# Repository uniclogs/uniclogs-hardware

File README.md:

# University Class Open Ground Station
UniClOGS ground station hardware for both RF and antenna positioning

## OreSat Ground Station Infrastructure

OreSat will utilize two ground stations for this project, a primary station, and a fully-capable secondary station. The primary station is being constructed by the students involved in the project and will be located on the Portland State University Engineering Building. The secondary station is an existing amateur satellite ground station located at a different location for spatial diversity. It can be used to help verify and check out the primary station as construction progresses, and serve as a backup to the primary station. The two stations are identical.

## RF Links

The ground station infrastructure provides two communications functions between the ground and the spacecraft, (1) downlink communications on UHF for the Telemetry Beacons and Command Responses from the spacecraft, (2) uplink communications on L-Band for the Commands to the spacecraft, and (3) downlink communications on S-band for mission payload and camera data.

The UHF component is centered in the 435 to 438 MHz amateur spacecraft service band and utilizes a circular polarized directional Yagi antenna with a RHCP/LHCP polarization sense switch. The L-Band component is centered in the 1260 to 1270 MHz amateur spacecraft service band designated for uplink only, and utilizes a RHCP circular polarized 2x2 helix array. All of this is mounted on an azimuth/elevation antenna positioner. A coax switch connects the UHF antenna to either a Low Noise Amplifier (LNA) for receiving, or a Power Amplifier (PA) for transmitting. The LNA and PA is then connected to a Software Defined Radio (SDR) that provides both UHF RF input and output signals. The L-Band antenna is directly connected to a PA for transmitting only, and then to the same SDR to provide the L Band RF signal.

The S-Band component is centered on 2.4 to 2.43 GHz amateur spacecraft service spectrum. A 0.5 meter parabolic reflector with a RHCP/LHCP feed is mounted on the same antenna positioner as the UHF and L-Band antenna. A coax switch is used to select RHCP or LHCP signal from the feed, is then fed to a bidirectional PA/LNA. The PA/LNA is connected to a ATH9K IEEE 802.11b adapter that provides both the S-Band RF downlink receiver and uplink transmitter signals.

The SDR used for UHF and L-Band is the LimeSDR from LimeMicro, which utilizes GnuRadio for modulation and demodulation. The emission type is GFSK at 50 kb/s, and was chosen for the capability of the Engineering transceiver radio on the spacecraft, an acceptable performance indicated by the link budget, and is somewhat common in the amateur satellite community.

## Antenna positioner

An antenna positioner controller is used to aim the antenna array and is interfaced serially using the EasyComm control protocol accessible through the HamLib control library. The positioner controller is based on the Open Source hardware/software project by K3NG, and provides the ability for tracking control through HamLib _rotctld_ both locally using GPredict, or by the SatNOGS Client software which provides interconnectivity to the SatNOGS system over the Internet.

## GnuRadio 

Data is passed into/out of the ground station radio through GnuRadio ModCod blocks and can provide raw IQ sample files from the payload data. Doppler shift can be compensated for in real time using the tracking software and an XML/RPC server in GnuRadio.

## Data

The Engineering Control/Telemetry subsystem provides telemetry data to the ground in two forms, a GFSK modulated data frame in response to a command request, and a very short Morse code (CW) modulated telemetry sequence and satellite ID if no activity is present for a given period of time. This Morse code ID allows the satellite to be heard by the general amateur radio community and will help with identifying the satellite once on orbit. There are several satellite housekeeping commands that can be sent up from the ground to control power, attitude and payload functions, and most importantly a command to reliably shut off all RF transmissions if required. All commands up to the satellite are authenticated for security.

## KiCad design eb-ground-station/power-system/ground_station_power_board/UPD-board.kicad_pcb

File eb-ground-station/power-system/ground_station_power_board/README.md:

# Station Power Board

This board controls all of the switching of power to components in the ground station.
It accepts it's commands through an I2C interface on the Stationd computer.

The switching is acomplished through 3 I2C GPIO device setup as 24 output bits. The
bits control mosfet switches provideing both 5VDC and 12VDC circuits.

The board also has an A/D to monitor the RF Power Amplifiers output power detectors. The
characteristics of this power measurement is detailed in the power amplifier testing
spreadsheet unfer RF-systems.

Finally this board provides a temperature measurement of the system enclosures environment.

See further documentation in the docs folder

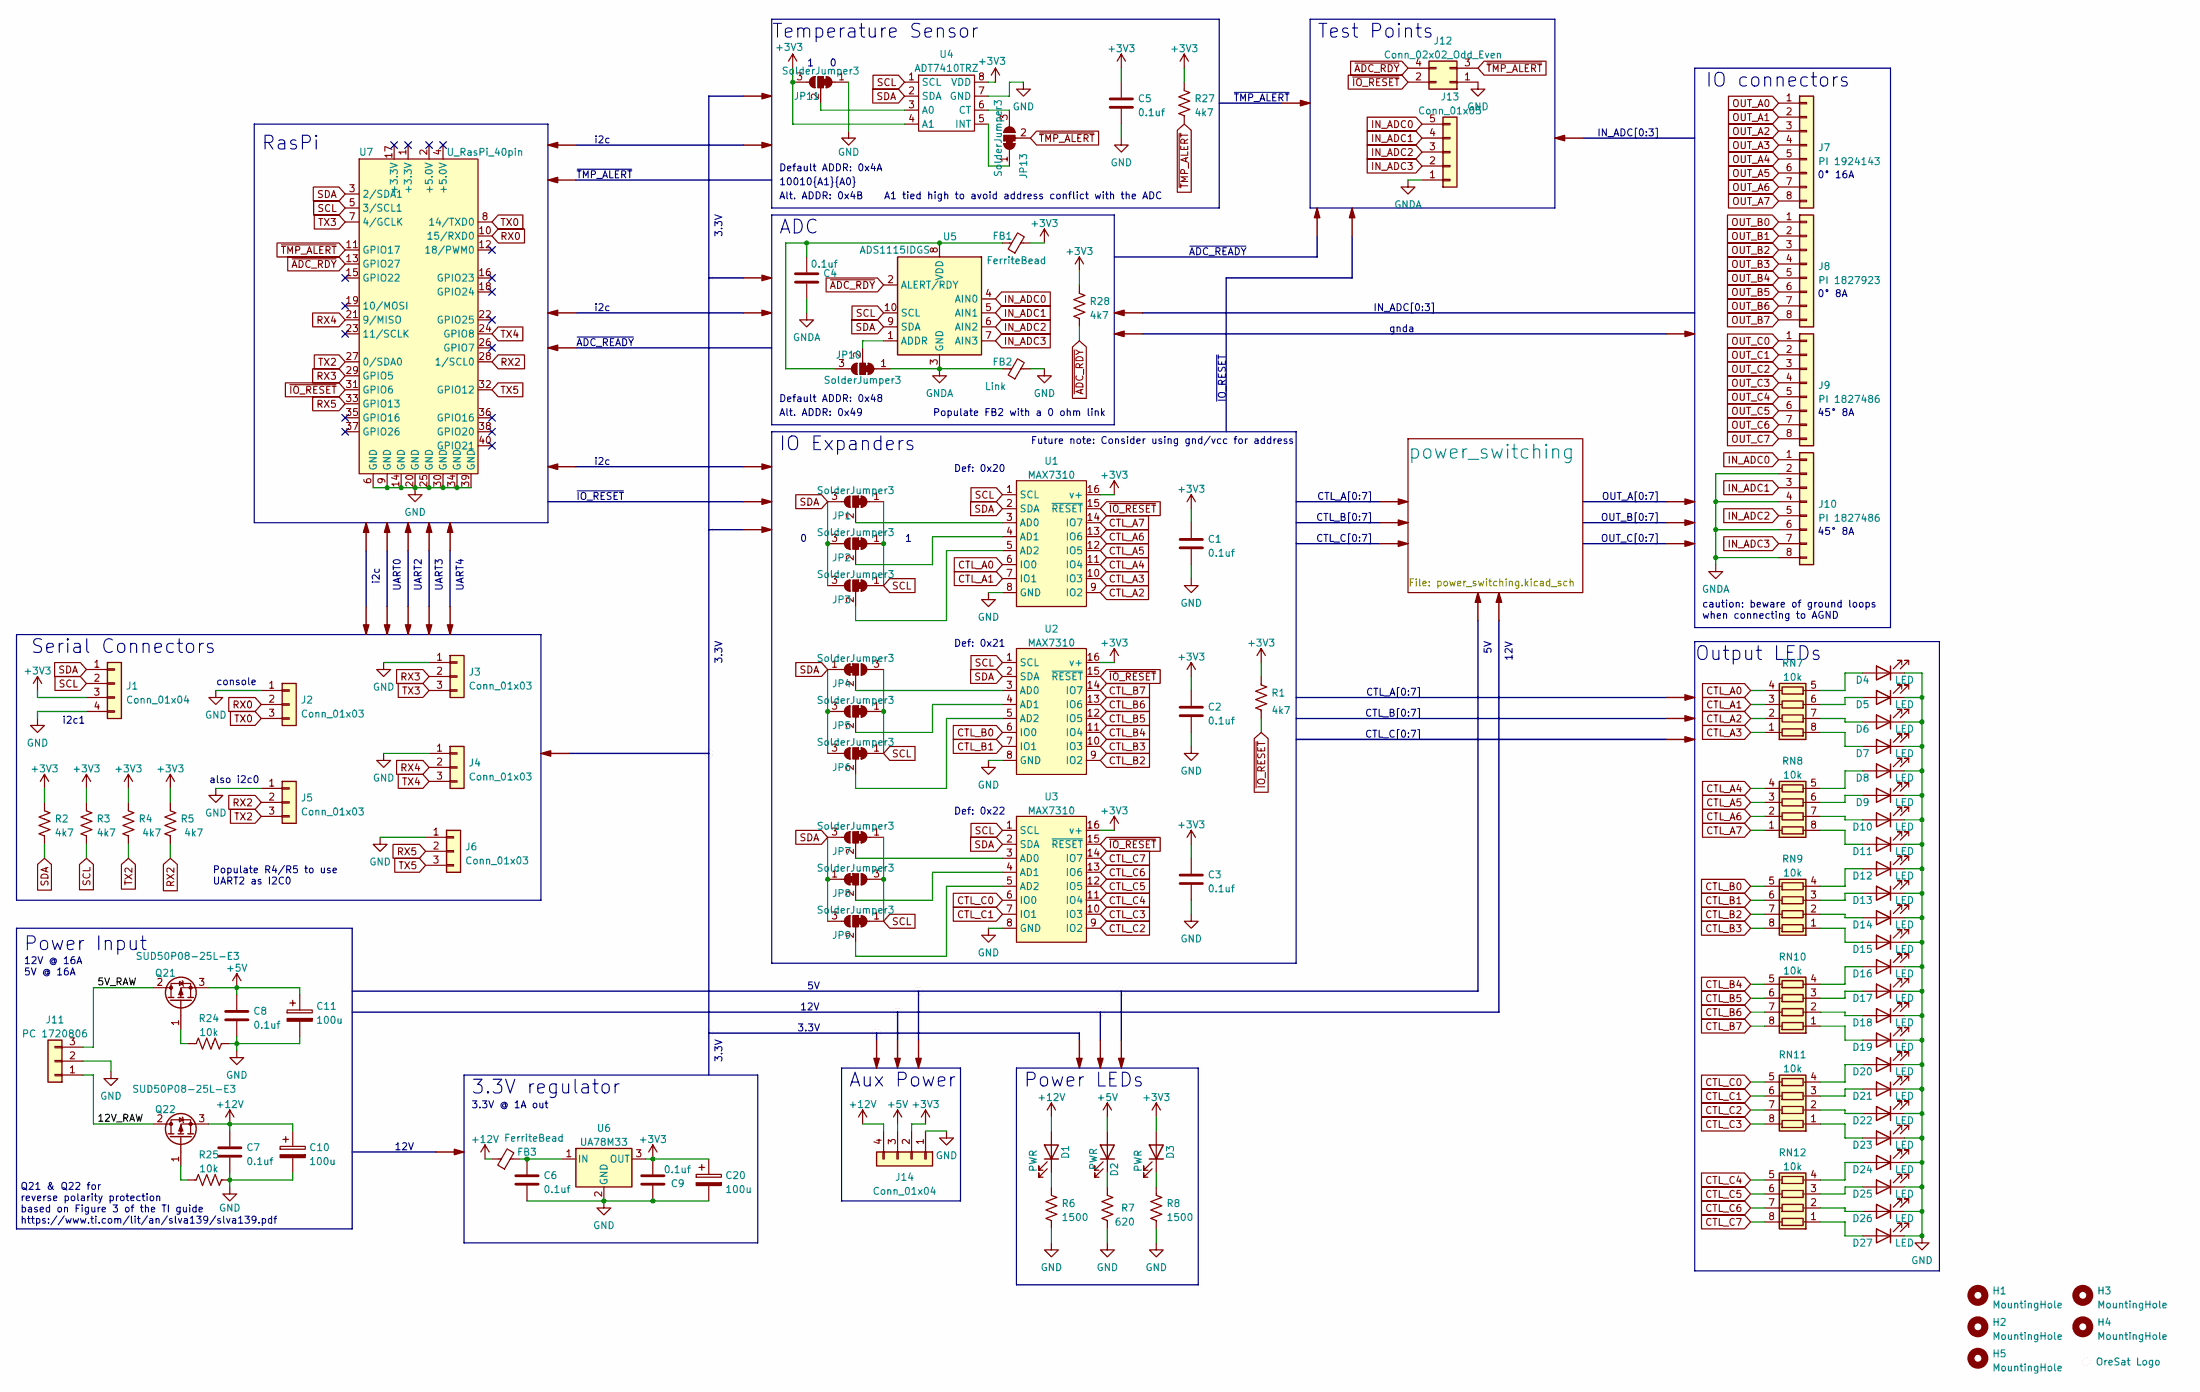
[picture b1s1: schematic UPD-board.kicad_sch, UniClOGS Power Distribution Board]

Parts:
C1, C2, C3, C4, C5, C6, C7, C8, C9: 0.1uf; C_0603_1608Metric; MPN CL10B104KB8NNWC
C10, C11, C20: 100u; CP_Elec_6.3x5.9; MPN 865080445010
D1, D2, D3: PWR; LED_0603_1608Metric
D4, D5, D6, D7, D8, D9, D10, D11, D12, D13, D14, D15, D16, D17, D18, D19, D20, D21, D22, D23, D24, D25, D26, D27: LED; LED_0603_1608Metric
FB1, FB3: FerriteBead; C_0805_2012Metric; MPN WLBD2012HCU310TH
FB2: Link; R_0805_2012Metric
H1, H2, H3, H4, H5: MountingHole; H-MCMASTER-94100A150
J1, J14: Conn_01x04; PinHeader_1x04_P2.54mm_Vertical
J2, J3, J4, J5, J6: Conn_01x03; PinHeader_1x03_P2.54mm_Vertical
J7: PI 1924143; J_PhoenixContact_MC_1,5_8-GF-5.08_1x08_P5.08mm_Horizontal_T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
J8: PI 1827923; PhoenixContact_MC_1,5_8-GF-3.81_1x08_P3.81mm_Horizontal_Thr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
J9, J10: PI 1827486; J_PhoenixContact_MC_1,5_8-GF-3.81_1x08_P3.81mm_45degree_Thr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
J11: PC 1720806; PhoenixContact_GMSTBA_2,5_3-G-7,62_1x03_P7.62mm_Horizontal
J12: Conn_02x02_Odd_Even; PinHeader_2x02_P2.54mm_Vertical
J13: Conn_01x05; PinHeader_1x05_P2.54mm_Vertical
JP1, JP2, JP3, JP4, JP5, JP6, JP7, JP8, JP9, JP10, JP11, JP13: SolderJumper3; SolderJumper-3_P1.3mm_Bridged12_Pad1.0x1.5mm
LOGO1: OreSat Logo; logo-small
Q21, Q22: SUD50P08-25L-E3; TO-252-3_TabIsPin2
R1, R2, R3, R4, R5, R27, R28: 4k7; R_0603_1608Metric
R6, R8: 1500; R_0603_1608Metric
R7: 620; R_0603_1608Metric
R24, R25: 10k; R_0603_1608Metric
RN7, RN8, RN9, RN10, RN11, RN12: 10k; R_Array_Convex_4x0603; MPN RAVF164DJT10K0
U1, U2, U3: MAX7310; TSSOP-16_4.4x5mm_P0.65mm; MPN MAX7310ATE+T
U4: ADT7410TRZ; SOIC-8_3.9x4.9mm_P1.27mm
U5: ADS1115IDGS; TSSOP-10_3x3mm_P0.5mm
U6: UA78M33; SOT-223-3_TabPin2
U7: U_RasPi_40pin; IDC-Header_2x20_P2.54mm_Vertical

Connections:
+3V3: C1.1, C2.1, C3.1, C5.1, C9.1, C20.1, D3.2 (A), FB1.2, J1.3, J14.2, JP11.3 (B), R1.1, R2.1, R3.1, R4.1, R5.1, R27.1, R28.1, U1.16 (v+), U2.16 (v+), U3.16 (v+), U4.4 (A1), U4.8 (VDD), U6.3 (OUT); also elsewhere on the board
+5V: C8.2, C11.1, D2.2 (A), J14.3, Q21.3 (S); also elsewhere on the board
+12V: C7.1, C10.1, D1.2 (A), FB3.1, J14.4, Q22.3 (S); also elsewhere on the board
/5V_RAW: J11.3, Q21.2 (D)
/12V_RAW: J11.1, Q22.2 (D)
CTL_A0: RN7.4 (R4.1), U1.6 (IO0); also elsewhere on the board
CTL_A1: RN7.3 (R3.1), U1.7 (IO1); also elsewhere on the board
CTL_A2: RN7.2 (R2.1), U1.9 (IO2); also elsewhere on the board
CTL_A3: RN7.1 (R1.1), U1.10 (IO3); also elsewhere on the board
CTL_A4: RN8.4 (R4.1), U1.11 (IO4); also elsewhere on the board
CTL_A5: RN8.3 (R3.1), U1.12 (IO5); also elsewhere on the board
CTL_A6: RN8.2 (R2.1), U1.13 (IO6); also elsewhere on the board
CTL_A7: RN8.1 (R1.1), U1.14 (IO7); also elsewhere on the board
CTL_B0: RN9.5 (R4.2), U2.6 (IO0); also elsewhere on the board
CTL_B1: RN9.6 (R3.2), U2.7 (IO1); also elsewhere on the board
CTL_B2: RN9.7 (R2.2), U2.9 (IO2); also elsewhere on the board
CTL_B3: RN9.8 (R1.2), U2.10 (IO3); also elsewhere on the board
CTL_B4: RN10.5 (R4.2), U2.11 (IO4); also elsewhere on the board
CTL_B5: RN10.6 (R3.2), U2.12 (IO5); also elsewhere on the board
CTL_B6: RN10.7 (R2.2), U2.13 (IO6); also elsewhere on the board
CTL_B7: RN10.8 (R1.2), U2.14 (IO7); also elsewhere on the board
CTL_C0: RN11.5 (R4.2), U3.6 (IO0); also elsewhere on the board
CTL_C1: RN11.6 (R3.2), U3.7 (IO1); also elsewhere on the board
CTL_C2: RN11.7 (R2.2), U3.9 (IO2); also elsewhere on the board
CTL_C3: RN11.8 (R1.2), U3.10 (IO3); also elsewhere on the board
CTL_C4: RN12.5 (R4.2), U3.11 (IO4); also elsewhere on the board
CTL_C5: RN12.6 (R3.2), U3.12 (IO5); also elsewhere on the board
CTL_C6: RN12.7 (R2.2), U3.13 (IO6); also elsewhere on the board
CTL_C7: RN12.8 (R1.2), U3.14 (IO7); also elsewhere on the board
GND: C1.2, C2.2, C3.2, C5.2, C6.2, C7.2, C8.1, C9.2, C10.2, C11.2, C20.2, D4.1 (K), D5.1 (K), D6.1 (K), D7.1 (K), D8.1 (K), D9.1 (K), D10.1 (K), D11.1 (K), D12.1 (K), D13.1 (K), D14.1 (K), D15.1 (K), D16.1 (K), D17.1 (K), D18.1 (K), D19.1 (K), D20.1 (K), D21.1 (K), D22.1 (K), D23.1 (K), D24.1 (K), D25.1 (K), D26.1 (K), D27.1 (K), FB2.2, J1.4, J2.1, J3.1, J4.1, J5.1, J6.1, J11.2, J12.1, J14.1, JP11.1 (A), R6.1, R7.2, R8.1, R24.1, R25.1, U1.8 (GND), U2.8 (GND), U3.8 (GND), U4.7 (GND), U6.2 (GND), U7.6 (GND), U7.9 (GND), U7.14 (GND), U7.20 (GND), U7.25 (GND), U7.30 (GND), U7.34 (GND), U7.39 (GND); also elsewhere on the board
GNDA: C4.2, FB2.1, J10.2, J10.4, J10.6, J10.8, J13.1, JP10.1 (A), U5.3 (GND)
IN_ADC0: J10.1, J13.5, U5.4 (AIN0)
IN_ADC1: J10.3, J13.4, U5.5 (AIN1)
IN_ADC2: J10.5, J13.3, U5.6 (AIN2)
IN_ADC3: J10.7, J13.2, U5.7 (AIN3)
unnamed: C4.1, FB1.1, JP10.3 (B), U5.8 (VDD)
unnamed: C6.1, FB3.2, U6.1 (IN)
unnamed: D1.1 (K), R6.2
unnamed: D2.1 (K), R7.1
unnamed: D3.1 (K), R8.2
unnamed: D4.2 (A), RN7.5 (R4.2)
unnamed: D5.2 (A), RN7.6 (R3.2)
unnamed: D6.2 (A), RN7.7 (R2.2)
unnamed: D7.2 (A), RN7.8 (R1.2)
unnamed: D8.2 (A), RN8.5 (R4.2)
unnamed: D9.2 (A), RN8.6 (R3.2)
unnamed: D10.2 (A), RN8.7 (R2.2)
unnamed: D11.2 (A), RN8.8 (R1.2)
unnamed: D12.2 (A), RN9.4 (R4.1)
unnamed: D13.2 (A), RN9.3 (R3.1)
unnamed: D14.2 (A), RN9.2 (R2.1)
unnamed: D15.2 (A), RN9.1 (R1.1)
unnamed: D16.2 (A), RN10.4 (R4.1)
unnamed: D17.2 (A), RN10.3 (R3.1)
unnamed: D18.2 (A), RN10.2 (R2.1)
unnamed: D19.2 (A), RN10.1 (R1.1)
unnamed: D20.2 (A), RN11.4 (R4.1)
unnamed: D21.2 (A), RN11.3 (R3.1)
unnamed: D22.2 (A), RN11.2 (R2.1)
unnamed: D23.2 (A), RN11.1 (R1.1)
unnamed: D24.2 (A), RN12.4 (R4.1)
unnamed: D25.2 (A), RN12.3 (R3.1)
unnamed: D26.2 (A), RN12.2 (R2.1)
unnamed: D27.2 (A), RN12.1 (R1.1)
unnamed: JP1.2 (C), U1.3 (AD0)
unnamed: JP2.2 (C), U1.4 (AD1)
unnamed: JP3.2 (C), U1.5 (AD2)
unnamed: JP4.2 (C), U2.3 (AD0)
unnamed: JP5.2 (C), U2.4 (AD1)
unnamed: JP6.2 (C), U2.5 (AD2)
unnamed: JP7.2 (C), U3.3 (AD0)
unnamed: JP8.2 (C), U3.4 (AD1)
unnamed: JP9.2 (C), U3.5 (AD2)
unnamed: JP10.2 (C), U5.1 (ADDR)
unnamed: JP11.2 (C), U4.3 (A0)
unnamed: JP13.1 (A), U4.5 (INT)
unnamed: JP13.3 (B), U4.6 (CT)
unnamed: Q21.1 (G), R24.2
unnamed: Q22.1 (G), R25.2
OUT_A0: J7.1; also elsewhere on the board
OUT_A1: J7.2; also elsewhere on the board
OUT_A2: J7.3; also elsewhere on the board
OUT_A3: J7.4; also elsewhere on the board
OUT_A4: J7.5; also elsewhere on the board
OUT_A5: J7.6; also elsewhere on the board
OUT_A6: J7.7; also elsewhere on the board
OUT_A7: J7.8; also elsewhere on the board
OUT_B0: J8.1; also elsewhere on the board
OUT_B1: J8.2; also elsewhere on the board
OUT_B2: J8.3; also elsewhere on the board
OUT_B3: J8.4; also elsewhere on the board
OUT_B4: J8.5; also elsewhere on the board
OUT_B5: J8.6; also elsewhere on the board
OUT_B6: J8.7; also elsewhere on the board
OUT_B7: J8.8; also elsewhere on the board
OUT_C0: J9.1; also elsewhere on the board
OUT_C1: J9.2; also elsewhere on the board
OUT_C2: J9.3; also elsewhere on the board
OUT_C3: J9.4; also elsewhere on the board
OUT_C4: J9.5; also elsewhere on the board
OUT_C5: J9.6; also elsewhere on the board
OUT_C6: J9.7; also elsewhere on the board
OUT_C7: J9.8; also elsewhere on the board
RX0: J2.2, U7.10 (15/RXD0)
RX2: J5.2, R5.2, U7.28 (1/SCL0)
RX3: J3.2, U7.29 (GPIO5)
RX4: J4.2, U7.21 (9/MISO)
RX5: J6.2, U7.33 (GPIO13)
SCL: J1.2, JP1.1 (A), JP2.1 (A), JP3.1 (A), JP4.3 (B), JP5.1 (A), JP6.1 (A), JP7.1 (A), JP8.3 (B), JP9.1 (A), R3.2, U1.1 (SCL), U2.1 (SCL), U3.1 (SCL), U4.1 (SCL), U5.10 (SCL), U7.5 (3/SCL1)
SDA: J1.1, JP1.3 (B), JP2.3 (B), JP3.3 (B), JP4.1 (A), JP5.3 (B), JP6.3 (B), JP7.3 (B), JP8.1 (A), JP9.3 (B), R2.2, U1.2 (SDA), U2.2 (SDA), U3.2 (SDA), U4.2 (SDA), U5.9 (SDA), U7.3 (2/SDA1)
TX0: J2.3, U7.8 (14/TXD0)
TX2: J5.3, R4.2, U7.27 (0/SDA0)
TX3: J3.3, U7.7 (4/GCLK)
TX4: J4.3, U7.24 (GPIO8)
TX5: J6.3, U7.32 (GPIO12)
~ADC_RDY: J12.4, R28.2, U5.2 (ALERT/RDY), U7.13 (GPIO27)
~IO_RESET: J12.2, R1.2, U1.15 (~RESET), U2.15 (~RESET), U3.15 (~RESET), U7.31 (GPIO6)
~TMP_ALERT: J12.3, JP13.2 (C), R27.2, U7.11 (GPIO17)

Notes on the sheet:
12V
UART4
OUT_A[0:7]
~{ADC_READY}
3.3V
Power Input
UART2
45° 8A
Test Points
Alt. ADDR: 0x4B
Def: 0x20
3.3V @ 1A out
OUT_C[0:7]
Serial Connectors
OUT_B[0:7]
Def: 0x21
0° 16A
also i2c0
CTL_A[0:7]
Def: 0x22
CTL_C[0:7]
Temperature Sensor
CTL_B[0:7]
UART0
12V @ 16A 5V @ 16A
caution: beware of ground loops when connecting to AGND
IN_ADC[0:3]
0° 8A
A1 tied high to avoid address conflict with the ADC
Alt. ADDR: 0x49
Output LEDs
~{TMP_ALERT}
RasPi
i2c
Aux Power
Populate R4/R5 to use UART2 as I2C0
Default ADDR: 0x48
IO connectors
Power LEDs
~{IO_RESET}

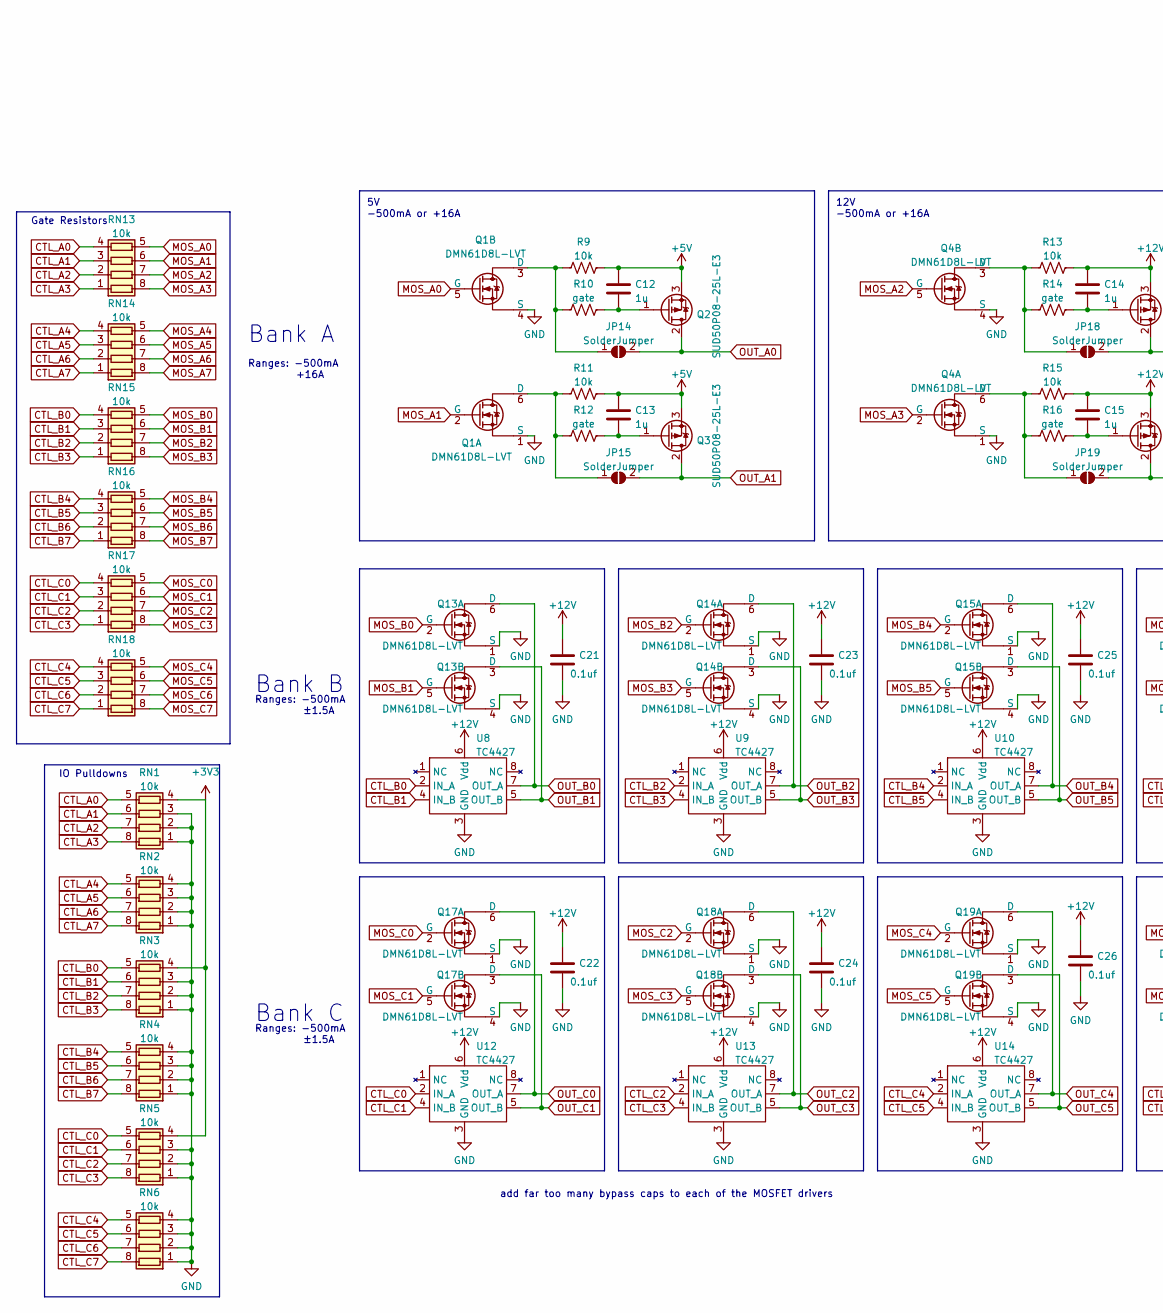
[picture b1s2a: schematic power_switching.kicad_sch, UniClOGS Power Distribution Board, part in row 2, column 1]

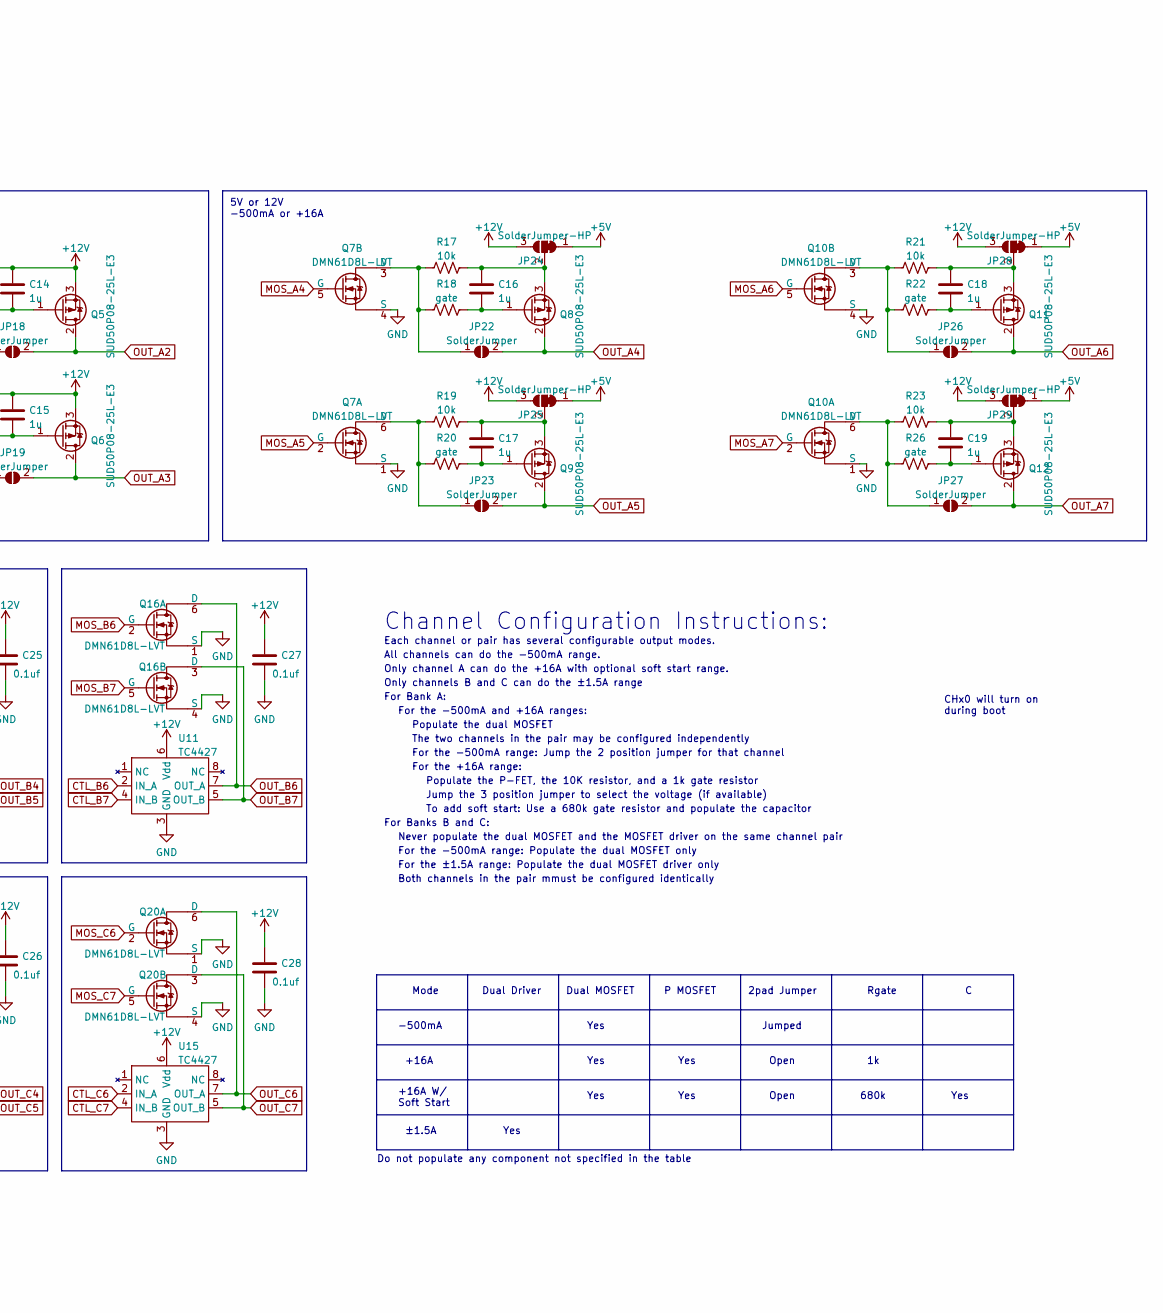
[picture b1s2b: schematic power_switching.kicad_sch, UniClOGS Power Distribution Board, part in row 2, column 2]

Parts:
C12, C13, C14, C15, C16, C17, C18, C19: 1u; C_0603_1608Metric; MPN CL10B105KA8NNNC
C21, C22, C23, C24, C25, C26, C27, C28: 0.1uf; C_0603_1608Metric; MPN CL10B104KB8NNWC
JP14, JP15, JP18, JP19, JP22, JP23, JP26, JP27: SolderJumper; SolderJumper-2_P1.3mm_Open_RoundedPad1.0x1.5mm
JP24, JP25, JP28, JP29: SolderJumper-HP; JP-SOLDER-2way-HP
Q1, Q4, Q7, Q10, Q13, Q14, Q15, Q16, Q17, Q18, Q19, Q20: DMN61D8L-LVT; TSOT26-6
Q2, Q3, Q5, Q6, Q8, Q9, Q11, Q12: SUD50P08-25L-E3; TO-252-3_TabIsPin2
R9, R11, R13, R15, R17, R19, R21, R23: 10k; R_0603_1608Metric
R10, R12, R14, R16, R18, R20, R22, R26: gate; R_0603_1608Metric
RN1, RN2, RN3, RN4, RN5, RN6, RN13, RN14, RN15, RN16, RN17, RN18: 10k; R_Array_Convex_4x0603; MPN RAVF164DJT10K0
U8, U9, U10, U11, U12, U13, U14, U15: TC4427; MSOP-8_3x3mm_P0.65mm

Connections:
+3V3: RN1.4 (R4.1), RN3.4 (R4.1), RN5.4 (R4.1); also elsewhere on the board
+5V: C12.1, C13.1, JP24.1 (A), JP25.1 (A), JP28.1 (A), JP29.1 (A), Q2.3 (S), Q3.3 (S), R9.2, R11.2; also elsewhere on the board
+12V: C14.1, C15.1, C21.1, C22.1, C23.1, C24.1, C25.1, C26.1, C27.1, C28.1, JP24.3 (B), JP25.3 (B), JP28.3 (B), JP29.3 (B), Q5.3 (S), Q6.3 (S), R13.2, R15.2, U8.6 (Vdd), U9.6 (Vdd), U10.6 (Vdd), U11.6 (Vdd), U12.6 (Vdd), U13.6 (Vdd), U14.6 (Vdd), U15.6 (Vdd); also elsewhere on the board
CTL_A0: RN1.5 (R4.2), RN13.4 (R4.1); also elsewhere on the board
CTL_A1: RN1.6 (R3.2), RN13.3 (R3.1); also elsewhere on the board
CTL_A2: RN1.7 (R2.2), RN13.2 (R2.1); also elsewhere on the board
CTL_A3: RN1.8 (R1.2), RN13.1 (R1.1); also elsewhere on the board
CTL_A4: RN2.5 (R4.2), RN14.4 (R4.1); also elsewhere on the board
CTL_A5: RN2.6 (R3.2), RN14.3 (R3.1); also elsewhere on the board
CTL_A6: RN2.7 (R2.2), RN14.2 (R2.1); also elsewhere on the board
CTL_A7: RN2.8 (R1.2), RN14.1 (R1.1); also elsewhere on the board
CTL_B0: RN3.5 (R4.2), RN15.4 (R4.1), U8.2 (IN_A); also elsewhere on the board
CTL_B1: RN3.6 (R3.2), RN15.3 (R3.1), U8.4 (IN_B); also elsewhere on the board
CTL_B2: RN3.7 (R2.2), RN15.2 (R2.1), U9.2 (IN_A); also elsewhere on the board
CTL_B3: RN3.8 (R1.2), RN15.1 (R1.1), U9.4 (IN_B); also elsewhere on the board
CTL_B4: RN4.5 (R4.2), RN16.4 (R4.1), U10.2 (IN_A); also elsewhere on the board
CTL_B5: RN4.6 (R3.2), RN16.3 (R3.1), U10.4 (IN_B); also elsewhere on the board
CTL_B6: RN4.7 (R2.2), RN16.2 (R2.1), U11.2 (IN_A); also elsewhere on the board
CTL_B7: RN4.8 (R1.2), RN16.1 (R1.1), U11.4 (IN_B); also elsewhere on the board
CTL_C0: RN5.5 (R4.2), RN17.4 (R4.1), U12.2 (IN_A); also elsewhere on the board
CTL_C1: RN5.6 (R3.2), RN17.3 (R3.1), U12.4 (IN_B); also elsewhere on the board
CTL_C2: RN5.7 (R2.2), RN17.2 (R2.1), U13.2 (IN_A); also elsewhere on the board
CTL_C3: RN5.8 (R1.2), RN17.1 (R1.1), U13.4 (IN_B); also elsewhere on the board
CTL_C4: RN6.5 (R4.2), RN18.4 (R4.1), U14.2 (IN_A); also elsewhere on the board
CTL_C5: RN6.6 (R3.2), RN18.3 (R3.1), U14.4 (IN_B); also elsewhere on the board
CTL_C6: RN6.7 (R2.2), RN18.2 (R2.1), U15.2 (IN_A); also elsewhere on the board
CTL_C7: RN6.8 (R1.2), RN18.1 (R1.1), U15.4 (IN_B); also elsewhere on the board
GND: C21.2, C22.2, C23.2, C24.2, C25.2, C26.2, C27.2, C28.2, Q1.1 (S), Q1.4 (S), Q4.1 (S), Q4.4 (S), Q7.1 (S), Q7.4 (S), Q10.1 (S), Q10.4 (S), Q13.1 (S), Q13.4 (S), Q14.1 (S), Q14.4 (S), Q15.1 (S), Q15.4 (S), Q16.1 (S), Q16.4 (S), Q17.1 (S), Q17.4 (S), Q18.1 (S), Q18.4 (S), Q19.1 (S), Q19.4 (S), Q20.1 (S), Q20.4 (S), RN1.1 (R1.1), RN1.2 (R2.1), RN1.3 (R3.1), RN2.1 (R1.1), RN2.2 (R2.1), RN2.3 (R3.1), RN2.4 (R4.1), RN3.1 (R1.1), RN3.2 (R2.1), RN3.3 (R3.1), RN4.1 (R1.1), RN4.2 (R2.1), RN4.3 (R3.1), RN4.4 (R4.1), RN5.1 (R1.1), RN5.2 (R2.1), RN5.3 (R3.1), RN6.1 (R1.1), RN6.2 (R2.1), RN6.3 (R3.1), RN6.4 (R4.1), U8.3 (GND), U9.3 (GND), U10.3 (GND), U11.3 (GND), U12.3 (GND), U13.3 (GND), U14.3 (GND), U15.3 (GND); also elsewhere on the board
MOS_A0: Q1.5 (G), RN13.5 (R4.2)
MOS_A1: Q1.2 (G), RN13.6 (R3.2)
MOS_A2: Q4.5 (G), RN13.7 (R2.2)
MOS_A3: Q4.2 (G), RN13.8 (R1.2)
MOS_A4: Q7.5 (G), RN14.5 (R4.2)
MOS_A5: Q7.2 (G), RN14.6 (R3.2)
MOS_A6: Q10.5 (G), RN14.7 (R2.2)
MOS_A7: Q10.2 (G), RN14.8 (R1.2)
MOS_B0: Q13.2 (G), RN15.5 (R4.2)
MOS_B1: Q13.5 (G), RN15.6 (R3.2)
MOS_B2: Q14.2 (G), RN15.7 (R2.2)
MOS_B3: Q14.5 (G), RN15.8 (R1.2)
MOS_B4: Q15.2 (G), RN16.5 (R4.2)
MOS_B5: Q15.5 (G), RN16.6 (R3.2)
MOS_B6: Q16.2 (G), RN16.7 (R2.2)
MOS_B7: Q16.5 (G), RN16.8 (R1.2)
MOS_C0: Q17.2 (G), RN17.5 (R4.2)
MOS_C1: Q17.5 (G), RN17.6 (R3.2)
MOS_C2: Q18.2 (G), RN17.7 (R2.2)
MOS_C3: Q18.5 (G), RN17.8 (R1.2)
MOS_C4: Q19.2 (G), RN18.5 (R4.2)
MOS_C5: Q19.5 (G), RN18.6 (R3.2)
MOS_C6: Q20.2 (G), RN18.7 (R2.2)
MOS_C7: Q20.5 (G), RN18.8 (R1.2)
unnamed: C12.2, Q2.1 (G), R10.2
unnamed: C13.2, Q3.1 (G), R12.2
unnamed: C14.2, Q5.1 (G), R14.2
unnamed: C15.2, Q6.1 (G), R16.2
unnamed: C16.1, JP24.2 (C), Q8.3 (S), R17.2
unnamed: C16.2, Q8.1 (G), R18.2
unnamed: C17.1, JP25.2 (C), Q9.3 (S), R19.2
unnamed: C17.2, Q9.1 (G), R20.2
unnamed: C18.1, JP28.2 (C), Q11.3 (S), R21.2
unnamed: C18.2, Q11.1 (G), R22.2
unnamed: C19.1, JP29.2 (C), Q12.3 (S), R23.2
unnamed: C19.2, Q12.1 (G), R26.2
unnamed: JP14.1 (A), Q1.3 (D), R9.1, R10.1
unnamed: JP15.1 (A), Q1.6 (D), R11.1, R12.1
unnamed: JP18.1 (A), Q4.3 (D), R13.1, R14.1
unnamed: JP19.1 (A), Q4.6 (D), R15.1, R16.1
unnamed: JP22.1 (A), Q7.3 (D), R17.1, R18.1
unnamed: JP23.1 (A), Q7.6 (D), R19.1, R20.1
unnamed: JP26.1 (A), Q10.3 (D), R21.1, R22.1
unnamed: JP27.1 (A), Q10.6 (D), R23.1, R26.1
OUT_A0: JP14.2 (B), Q2.2 (D); also elsewhere on the board
OUT_A1: JP15.2 (B), Q3.2 (D); also elsewhere on the board
OUT_A2: JP18.2 (B), Q5.2 (D); also elsewhere on the board
OUT_A3: JP19.2 (B), Q6.2 (D); also elsewhere on the board
OUT_A4: JP22.2 (B), Q8.2 (D); also elsewhere on the board
OUT_A5: JP23.2 (B), Q9.2 (D); also elsewhere on the board
OUT_A6: JP26.2 (B), Q11.2 (D); also elsewhere on the board
OUT_A7: JP27.2 (B), Q12.2 (D); also elsewhere on the board
OUT_B0: Q13.6 (D), U8.7 (OUT_A); also elsewhere on the board
OUT_B1: Q13.3 (D), U8.5 (OUT_B); also elsewhere on the board
OUT_B2: Q14.6 (D), U9.7 (OUT_A); also elsewhere on the board
OUT_B3: Q14.3 (D), U9.5 (OUT_B); also elsewhere on the board
OUT_B4: Q15.6 (D), U10.7 (OUT_A); also elsewhere on the board
OUT_B5: Q15.3 (D), U10.5 (OUT_B); also elsewhere on the board
OUT_B6: Q16.6 (D), U11.7 (OUT_A); also elsewhere on the board
OUT_B7: Q16.3 (D), U11.5 (OUT_B); also elsewhere on the board
OUT_C0: Q17.6 (D), U12.7 (OUT_A); also elsewhere on the board
OUT_C1: Q17.3 (D), U12.5 (OUT_B); also elsewhere on the board
OUT_C2: Q18.6 (D), U13.7 (OUT_A); also elsewhere on the board
OUT_C3: Q18.3 (D), U13.5 (OUT_B); also elsewhere on the board
OUT_C4: Q19.6 (D), U14.7 (OUT_A); also elsewhere on the board
OUT_C5: Q19.3 (D), U14.5 (OUT_B); also elsewhere on the board
OUT_C6: Q20.6 (D), U15.7 (OUT_A); also elsewhere on the board
OUT_C7: Q20.3 (D), U15.5 (OUT_B); also elsewhere on the board

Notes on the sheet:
Yes
Jumped
Populate the P-FET, the 10K resistor, and a 1k gate resistor
For the ±1.5A range: Populate the dual MOSFET driver only
Dual Driver
+16A
P MOSFET
5V -500mA or +16A
add far too many bypass caps to each of the MOSFET drivers
For Bank A:
Ranges: -500mA +16A
12V -500mA or +16A
5V or 12V -500mA or +16A
Jump the 3 position jumper to select the voltage (if available)
Each channel or pair has several configurable output modes.
For the -500mA range: Populate the dual MOSFET only
Open
Mode
Only channel A can do the +16A with optional soft start range.
Bank A
+16A W/ Soft Start
Do not populate any component not specified in the table
Dual MOSFET
IO Pulldowns
Only channels B and C can do the ±1.5A range
Gate Resistors
Channel Configuration Instructions:
To add soft start: Use a 680k gate resistor and populate the capacitor
All channels can do the -500mA range.
2pad Jumper
Bank B
Ranges: -500mA ±1.5A
CHx0 will turn on during boot
See design notes on how to populate this area of the circuit to configre output behavior
For the -500mA range: Jump the 2 position jumper for that channel
680k
Both channels in the pair mmust be configured identically
For the +16A range:
Rgate
Never populate the dual MOSFET and the MOSFET driver on the same channel pair

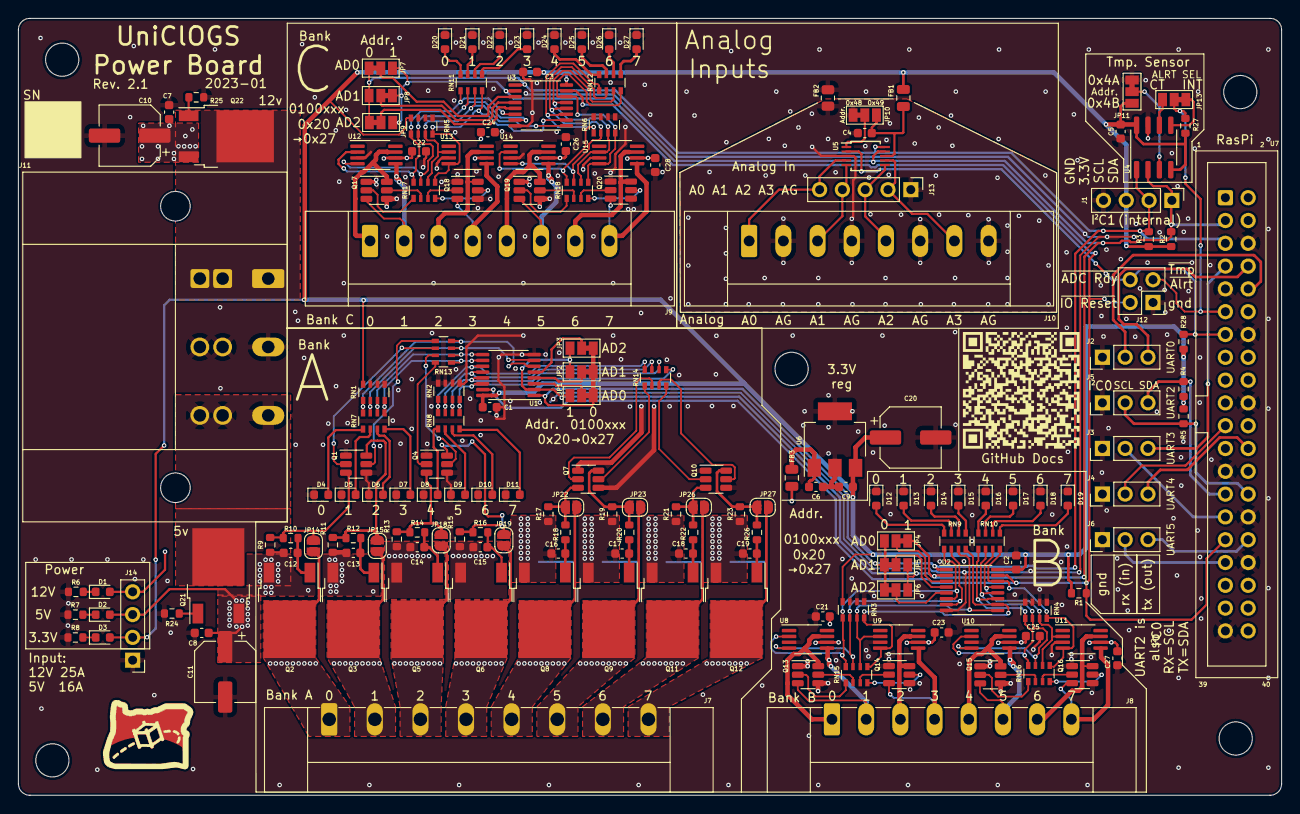
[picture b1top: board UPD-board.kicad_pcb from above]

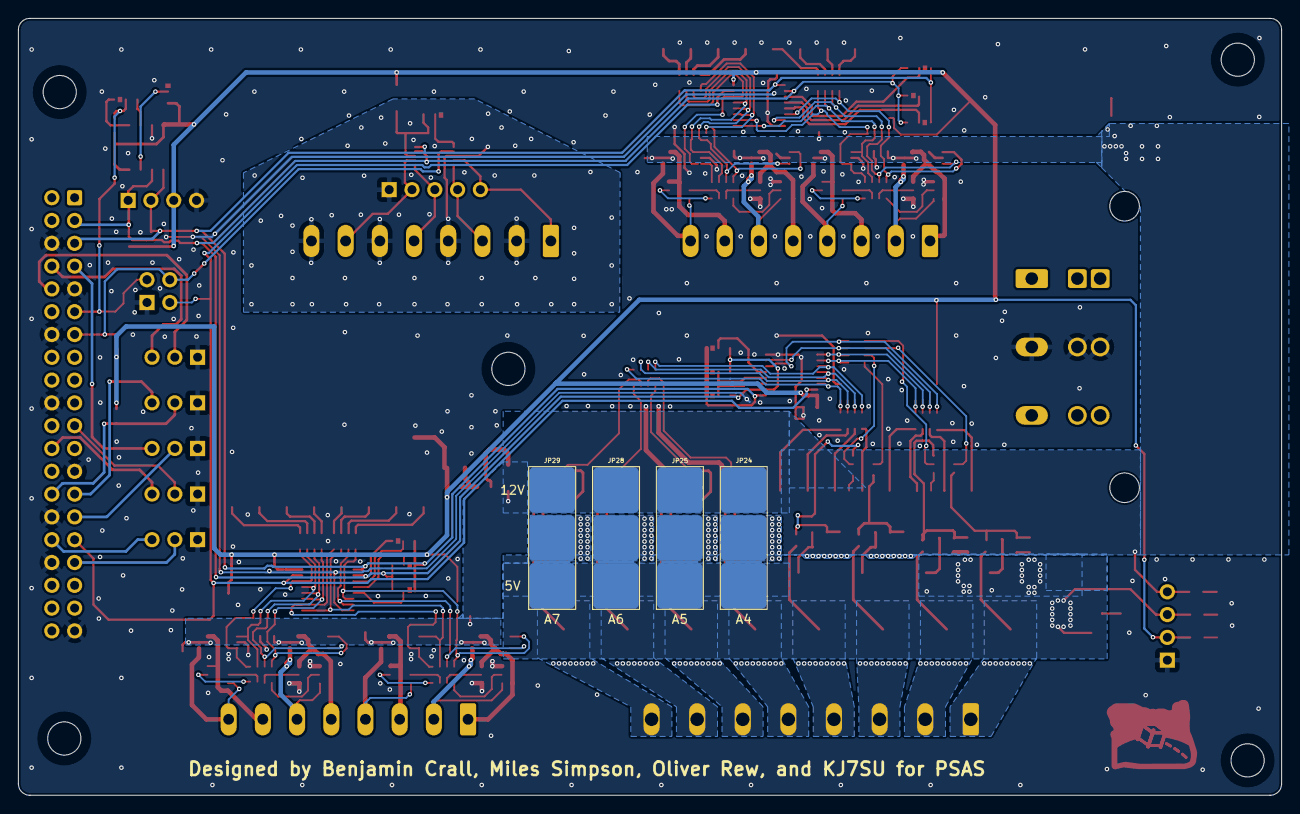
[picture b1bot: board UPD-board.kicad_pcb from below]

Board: 2 copper layers, 140.7 x 86.5 mm, 185 parts (4 on the bottom side), 162 nets.

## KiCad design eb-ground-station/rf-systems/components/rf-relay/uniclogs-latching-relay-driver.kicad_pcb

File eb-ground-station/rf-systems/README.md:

## RF Components

* Antennas
* Feedlines
* Low Noise Amplifier
* Power Amplifier
* Software Defined Radio (SDR)

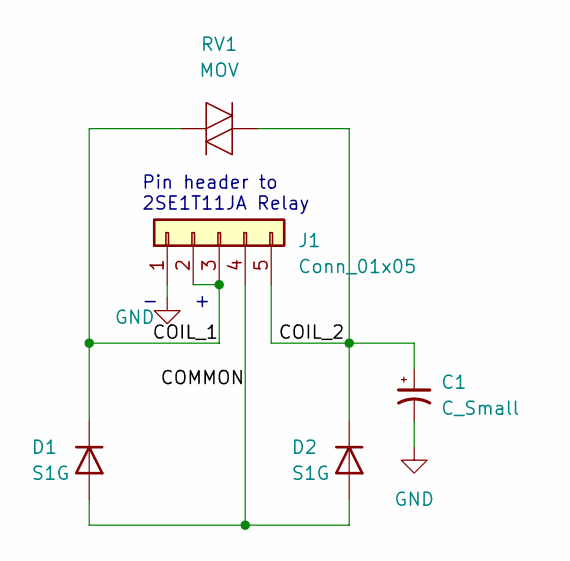
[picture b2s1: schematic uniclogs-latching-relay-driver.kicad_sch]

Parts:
C1: C_Small; CP_Elec_16x16.8
D1, D2: S1G; D_SMA
J1: Conn_01x05; 2-3_1x05_2.54mm
RV1: MOV; 2220_MOV

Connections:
/COIL_1: D1.1 (K), J1.2, J1.3, RV1.1
/COIL_2: C1.1, D2.1 (K), J1.5, RV1.2
/COMMON: D1.2 (A), D2.2 (A), J1.4
GND: C1.2, J1.1

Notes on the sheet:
Pin header to 2SE1T11JA Relay

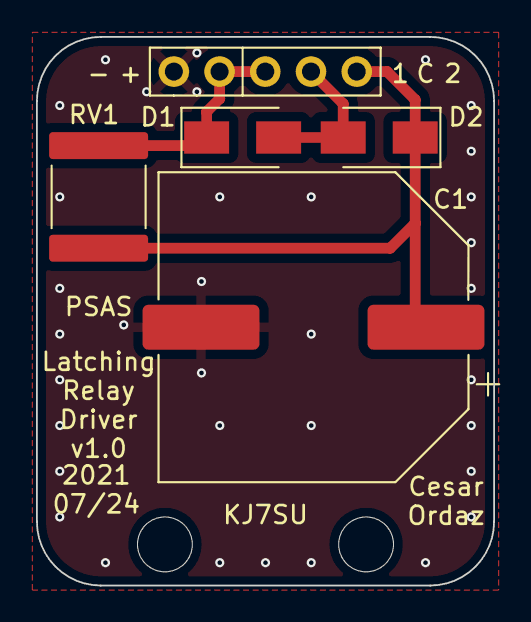
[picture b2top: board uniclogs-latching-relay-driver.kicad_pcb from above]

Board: 2 copper layers, 25.4 x 30.5 mm, 5 parts (0 on the bottom side), 4 nets.

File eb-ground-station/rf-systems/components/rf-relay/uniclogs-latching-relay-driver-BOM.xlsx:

UniClOGS Latching Relay Driver Board v1.0 BOM revision 0
Qty | Parts | MFR | MPN | Description | DIST | DPN | P/NP | Notes
1 | C1 | Panasonic | EEV-FK1H471M | CAP ALUM 470UF 20% 50V SMD | Digi-Key | P19506CT-ND | P
1 | RV1 | TDK Electronics | B72540V1140S262 | VARISTOR 22V 1.2KA 2220 | Digi-Key | 495-1461-1-ND | P
2 | D1, D2 | Diodes Incorporated | S1G-13-F | DIODE GEN PURP 400V 1A SMA | Digi-Key | S1G-FDICT-ND | P
